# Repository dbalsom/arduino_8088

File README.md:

# Arduino8088

### About Arduino8088
I've writtten a blog article that gives an overview of this project and how it is used.

https://martypc.blogspot.com/2023/06/hardware-validating-emulator.html

### Description

This project expands on the basic idea of controlling an Intel 8088 or NEC V20 CPU via GPIO pins to clock the CPU and read and write control and data signals.
This can be used to validate an emulator's accuracy, but also as a general method of exploring the operation of 8088 and V20 instructions and timings.

Where it differs from Raspberry Pi based projects is that it uses an Arduino DUE to supply enough GPIO pins to operate the 8088 in Maximum mode without requiring any shifters. This enables several useful signals to be read such as the QS0 & QS1 processor instruction queue status lines, which give us more insight into the internal state of the CPU. We can also enable inputs such as READY, NMI, INTR, and TEST, so we can in theory execute interrupts, emulate wait states, and perhaps simulate FPU and DMA operations.

The board supports an Intel 8288 bus controller which can produce bus signals, but this chip is optional as the sketch can perform i8288 emulation.

The original Arduino8088 board utilized an Arduino MEGA, but this board is now considered deprecated for this project. As of the current release, an [Arduino DUE](https://store.arduino.cc/products/arduino-due) should be used instead. Although the DUE has 3v GPIO, the current board design is modified for 3V operation.  The 80C88 itself tolerates 3V well, and i8288 emulation can be used if you lack a CMOS 8288.

I have been using this project to validate the cycle-accuracy of my PC emulator, MartyPC: https://github.com/dbalsom/martypc 

## Can the CPU be clocked fast enough?

In short, no. We are well past the published minimum cycle times when executing programs via a serial protocol, cycle by cycle. Some chips tolerate this better than others. When working with an Intel branded 8088, I noticed that effective address calculations were failing to add the displacement or index register, but otherwise functioned. I have had more luck with the AMD second-source 8088 CPUs, which seem to function perfectly under slow clocks although they will hang and need to be reset if not cycled for a several milliseconds. The issue is "dynamic logic" - logic gates that lose their state if not refrehsed electrically within a frequent enough interval. To be absolutely safe, it is best to use a fully CMOS process CPU such as the 80C88. 

## Credits

Inspired by and borrows from the Pi8088 validator created by Andreas Jonsson as part of the VirtualXT project:

https://github.com/andreas-jonsson/virtualxt/tree/develop/tools/validator/pi8088

A very similar project is homebrew8088's Raspberry Pi Hat:

https://github.com/homebrew8088/pi86

## To use

If you don't want to order and build the PCB, connect the GPIO pins to the CPU on a breadboard as specified in the KiCad project schematic.

The main Arduino8088 sketch, cpu_server, operates a simple binary serial protocol to execute operations on the CPU and read and write data, status and control signals. This is designed for integration with an emulator or instruction test generator.

Additionally there is a sketch, 'run_program', that will take any user-supplied register state and array of instruction bytes defined in the source code, execute it, and print cycle traces and final register state. This is useful for investigating the timing and operation of certain instructions without needing any external software integrations, however it is restricted in the number of memory reads or writes it can support, due to the limited RAM on the Arduino MEGA (8k!) 'run_program' does not currently support the DUE.

An example client for cpu_server is provded, written in Rust, in the client directory. It demonstrates how to upload arbitrary code to the Arduino8088 and display cycle traces. The client will emulate the entire address space and set up a basic IVT.

## PCB

KiCad project files for the PCB are supplied. 

In theory the board could also support an 8086 CPU. Version 1.1 adds a connection for the 8086's BHE pin, 
which indicates the size of the current bus transfer.  The cpu_server sketch and protocol still needs modification to support 16 bit data transfers and the longer queue length on the 8086.

Please read all the notes in the next section before ordering/assembling parts. Failure to heed warnings will cause damage to your Arduino.

# BOM
- A compatible CPU. For best results, use a CMOS CPU such as a Harris 80C88, Oki 80C88, or NEC V20 CPU. Beware of counterfeits on eBay and other online vendors.
A legitimate chip will not look shiny and new with perfect printing on it.

- (Optional) An Intel 8288 or OKI 82C88 Bus Controller. If not using an 8288, set the EMULATE_8288 flag in cpu_server.

- A set of Arduino stacking headers (also usable with DUE) 
https://www.amazon.com/Treedix-Stacking-Headers-Stackable-Compatible/dp/B08G4FGBPQ

- A DIP-40 and (optionally) DIP-20 socket
  - Optional: You can spring for a ZIF socket such as [https://www.amazon.com/-/en/gp/product/B00B886OZI](https://www.amazon.com/-/en/gp/product/B00B886OZI)

- (2x) 0805 0.047uf bypass capacitors
  https://www.mouser.com/ProductDetail/80-C0805C473KARAUTO

- (Optional) A 12mm, active buzzer with 7.6mm pin spacing. 

  - For DUE: A 3V piezoelectric, low power buzzer <= 6mA
    https://www.mouser.com/ProductDetail/Mallory-Sonalert/PK-11N40PQ?qs=SXHtpsd1MbZ%252B7jeUyAAOVA%3D%3D
    
  - For MEGA: Any 3-5V buzzer <= 30mA
    WARNING: Only connect an electromagnetic buzzer if using an Arduino MEGA.  The DUE has much lower GPIO max current supply.    

- (2x) 750Ohm resistors (for LEDs)
  https://www.mouser.com/ProductDetail/667-ERA-6AED751V

- (2x) Any 0805 ~2V LED of your choice with 1.8-1.9mA forward current
  - https://www.mouser.com/ProductDetail/604-APTD2012LCGCK (Green)
  - https://www.mouser.com/ProductDetail/604-APT2012LSECKJ4RV (Orange)
 
- RS232 board for debug output - choose gender based on your desired cabling
  - https://www.amazon.com/Ultra-Compact-RS232-Converter-1Mbps/dp/B074BMLM11 (male)
  - https://www.amazon.com/Ultra-Compact-RS232-Converter-Female/dp/B074BTGLJN (female)
  - WARNING: DO NOT connect 5V to rs232 board on DUE

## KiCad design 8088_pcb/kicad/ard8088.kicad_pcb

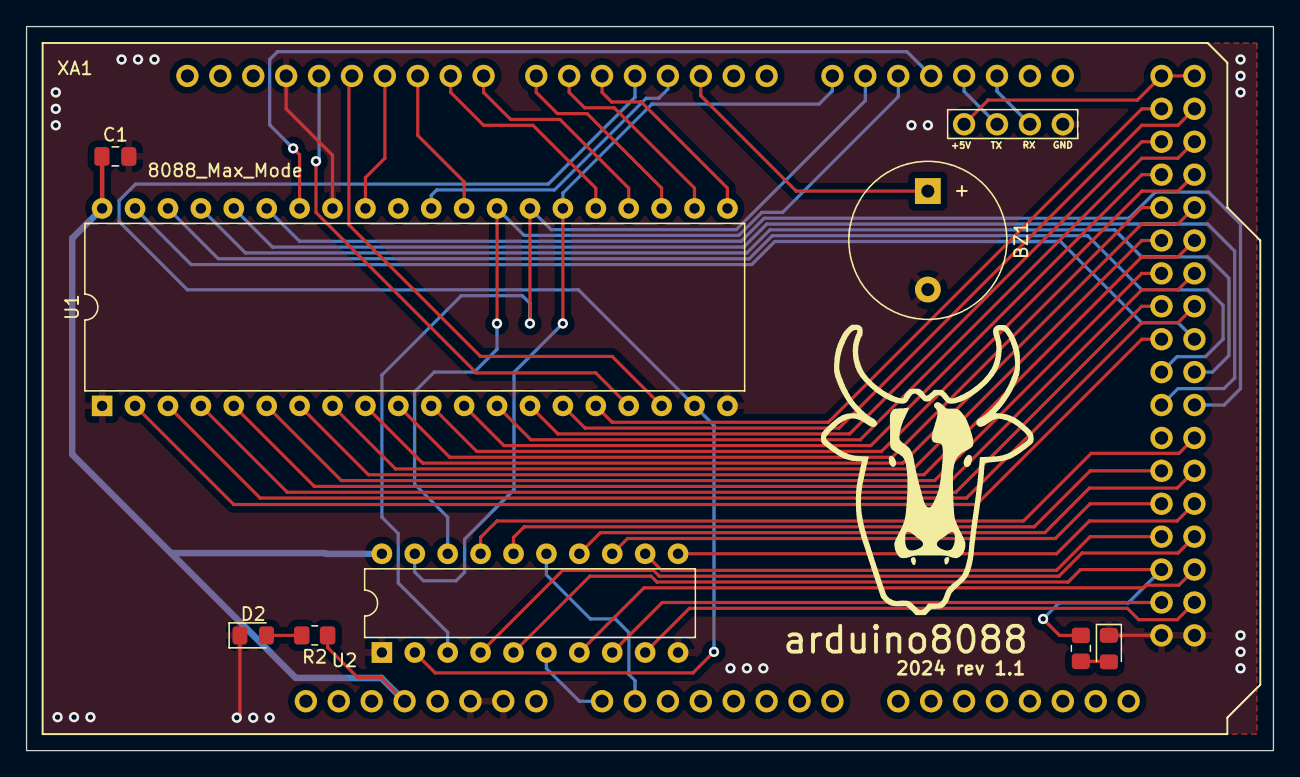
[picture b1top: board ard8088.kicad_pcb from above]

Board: 2 copper layers, 96.2 x 55.9 mm, 10 parts (1 on the bottom side), 55 nets.

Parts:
BZ1: Buzzer; Buzzer_12x9.5RM7.6
C1, C2: 0.1uf; C_0805_2012Metric_Pad1.18x1.45mm_HandSolder
D1, D2: LED; LED_0805_2012Metric_Pad1.15x1.40mm_HandSolder
R1, R2: R; R_0805_2012Metric_Pad1.20x1.40mm_HandSolder
U1: 8088_Max_Mode; DIP-40_W15.24mm
U2: 8288; DIP-20_W7.62mm
XA1: Arduino_Mega2560_Shield

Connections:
+5V: C1.1, C2.1, R2.1, U1.40 (VCC), U2.20 (VCC), XA1.3V3 (3.3V)
/+5Vactual: XA1.5V3 (5V), XA1.5V4 (5V), XA1.S0
/A8: U1.8 (A8), XA1.D30
/A9: U1.7 (A9), XA1.D31
/A10: U1.6 (A10), XA1.D32
/A11: U1.5 (A11), XA1.D33
/A12: U1.4 (A12), XA1.D34
/A13: U1.3 (A13), XA1.D35
/A14: U1.2 (A14), XA1.D36
/A15: U1.39 (A15), XA1.D37
/A16: U1.38 (A16/S3), XA1.D38
/A17: U1.37 (A17/S4), XA1.D39
/A18: U1.36 (A18/S5), XA1.D40
/A19: U1.35 (A19/S6), XA1.D41
/AD0: U1.16 (AD0), XA1.D22
/AD1: U1.15 (AD1), XA1.D23
/AD2: U1.14 (AD2), XA1.D24
/AD3: U1.13 (AD3), XA1.D25
/AD4: U1.12 (AD4), XA1.D26
/AD5: U1.11 (AD5), XA1.D27
/AD6: U1.10 (AD6), XA1.D28
/AD7: U1.9 (AD7), XA1.D29
/ALE: R1.1, U2.5 (ALE), XA1.D50
/CEN: U2.15 (CEN), XA1.A1
/CLK: U1.19 (CLK), U2.2 (CLK), XA1.D4
/DEN: U2.16 (DEN), XA1.D44
/DT/~R: U2.4 (DT/~R), XA1.D49
/INTR: U1.18 (INTR), XA1.D12
/MCE/~PDEN: U2.17 (MCE/~PDEN), XA1.D43
/NMI: U1.17 (NMI), XA1.D13
/QS1: U1.24 (QS1), XA1.D8
/QSO: U1.25 (QS0), XA1.D9
/READY: U1.22 (READY), XA1.D6
/RESET: U1.21 (RESET), XA1.D5
/S0: U1.26 (~S0), U2.19 (~S0), XA1.D14 (D14_TX3)
/S1: U1.27 (~S1), U2.3 (~S1), XA1.D15 (D15_RX3)
/S2: U1.28 (~S2), U2.18 (~S2), XA1.D16 (D16_TX2)
/ser0: XA1.D18 (D18_TX1), XA1.S1
/ser1: XA1.D19 (D19_RX1), XA1.S2
/~AEN: U2.6 (~AEN), XA1.A0
/~AIOWC: U2.12 (~AIOWC), XA1.D48
/~AMWC: U2.8 (~AMWC), XA1.D52
/~BHE: U1.34 (HIGH), XA1.D17 (D17_RX2)
/~INTA: U2.14 (~INTA), XA1.D45
/~IORC: U2.13 (~IORC), XA1.D46
/~IOWC: U2.11 (~IOWC), XA1.D47
/~LOCK: U1.29 (~LOCK), XA1.D10
/~MRDC: U2.7 (~MRDC), XA1.D51
/~MWTC: U2.9 (~MWTC), XA1.D53 (D53_SS)
/~RD: U1.32 (~RD), XA1.D11
/~RQ/~GT1: U1.30 (~RQ/~GT1), XA1.D3 (D3_INT1)
/~TEST: U1.23 (~TEST), XA1.D7
GND: BZ1.2 (+), C1.2, C2.2, D1.1 (K), D2.1 (K), U1.1 (GND), U1.20 (GND), U1.33 (MN/~MX), U2.1 (IOB), U2.10 (GND), XA1.GND1 (GND), XA1.GND2 (GND), XA1.GND3 (GND), XA1.GND5 (GND), XA1.GND6 (GND), XA1.S3
unnamed: D1.2 (A), R1.2
unnamed: D2.2 (A), R2.2

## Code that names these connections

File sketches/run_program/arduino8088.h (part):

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#define TEST_PIN 7
#define WRITE_TEST_PIN(x) (PORTH |= ((x) << 4))

// LOCK pin #10 is written by PORTB bit #4
#define LOCK_PIN 10
#define WRITE_LOCK_PIN(x) (PORTB |= ((x) << 4))

// INTR pin #12 is written by PORTB bit #6
#define INTR_PIN 12
#define WRITE_INTR_PIN(x) (PORTB |= ((x) << 6))

// NMI pin #13 is written to by PORTB bit #7
#define NMI_PIN 13
#define WRITE_NMI_PIN(x) (PORTB |= ((x) << 7))

// -------------------------- CPU Output pins ---------------------------------
#define RQ_PIN 3

// --------------------------8288 Control Inputs ------------------------------
#define AEN_PIN 54
#define READ_AEN_PIN ((PINF & 0x01) != 0)
#define WRITE_AEN_PIN(x) ((PINF |= x)

#define CEN_PIN 55
#define READ_CEN_PIN ((PINF & 0x02) != 0)
#define WRITE_CEN_PIN(x) ((PINF |= ((x) << 1))

// --------------------------8288 Control lines -------------------------------
// ALE pin #50 is read by PINB bit #3
#define ALE_PIN 50
#define READ_ALE_PIN ((PINB & 0x08) != 0)

// DTR pin #49 is read by PINL bit #0
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#define MCEPDEN_PIN 43
#define READ_MCEPDEN_PIN ((PINL & 0x40) != 0) 

// DEN pin #44 is read by PINL bit #5
#define DEN_PIN 44
#define READ_DEN_PIN ((PINL & 0x20) != 0)

// --------------------------8288 Command lines -------------------------------
// MRDC pin #51 is read by PINB bit #2
#define MRDC_PIN 51
#define READ_MRDC_PIN ((PINB & 0x04) != 0)

// AMWC pin #52 is read by PINB bit #1
#define AMWC_PIN 52
#define READ_AMWC_PIN ((PINB & 0x02) != 0)

// MWTC pin #53 is read by PINB bit #0
#define MWTC_PIN 53
#define READ_MWTC_PIN ((PINB & 0x01) != 0)

// IORC pin #46 is read by PINL bit #3
#define IORC_PIN 46
#define READ_IORC_PIN ((PINL & 0x08) != 0)

// AIOWC pin #48 is read by PINL bit #1
#define AIOWC_PIN 48
#define READ_AIOWC_PIN ((PINL & 0x02) != 0)

// IOWC pin #47 is read by PINL bit #2
#define IOWC_PIN 47
#define READ_IOWC_PIN ((PINL & 0x04) != 0)

// INTA pin #45 is read by PINL bit #4
#define INTA_PIN 45
#define READ_INTA_PIN ((PINL & 0x10) != 0)

// Address pins, used for slow address reading via digitalRead()
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
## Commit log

2022-12-23 Update README.md
    Initial README
2022-12-23 Initial commit of kicad project
2022-12-24 Move some CPU routines to lib.ino
2022-12-25 Revamp cycle trace output
2022-12-28 Add cpu server sketch
2023-01-01 Finalize op, debug buzzer
2023-01-01 Prefetch queue setup support
2023-01-13 Add prefetch prediction
2023-02-10 Update README for release of PCB
2023-02-10 Minor updates, release PCB
2023-03-11 fix overlapping ascii cmd
2023-03-11 Fix INTA pin read
2023-03-11 Fix resetting for PCB
2023-03-11 add RQ pin
2023-03-11 beep on setup
2023-03-11 Commit rust example client
2023-07-07 Changes to make it build with platformio:
    - renamed lib.ino to lib.cpp
    - moved some instances from h to cpp and replaced them with an 'extern
    ...'
    - u8/u16/u32 -> uintXX_t (afaik u8/16/32 are old Arduino style)
2023-07-07 Can talk to the Arduino-8088 device. At least 'get version' works.
2023-07-07 Revert "Can talk to the Arduino-8088 device. At least 'get version' works."
    This reverts commit 579fe1307c1a4322ab62a28683f89ae97f29882c.
    Was committed to the wrong branch.
2023-08-25 update types, move debugs to Serial1, add function
2024-05-11 Relicense as MIT
2024-05-11 Update rust client
2024-05-11 Update version
2024-05-11 Update gitignore
2024-05-11 Add base workspace
2024-05-11 update kicad project
2024-05-11 update cpu_server sketch
2024-05-11 upload images
2024-05-23 Numerous improvements to store program execution
2024-05-23 Add prefetching support to cpu client

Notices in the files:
sketches/run_program/arduino8088.h:
(C)2023 Daniel Balsom
This program is free software: you can redistribute it and/or modify
it under the terms of the GNU General Public License as published by
the Free Software Foundation, either version 3 of the License, or
(at your option) any later version.
